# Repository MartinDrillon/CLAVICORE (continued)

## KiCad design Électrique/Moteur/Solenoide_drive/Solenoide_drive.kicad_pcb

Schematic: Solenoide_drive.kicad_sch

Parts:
C1, C4, C5, C9: 22uF; C_1206_3216Metric; Mouser Part Number 187-CL31A226KAHNNNE
C2, C3, C8, C10, C14, C15, C16, C17, C18, C19, C20, C21, C22, C23, C24, C25, C26, C29, C33, C35, C37, C39, C42, C45, C46, C48, C50, C51, C54, C56, C58, C60, C62, C63, C66, C68, C70, C73, C74, C75, C78, C82, C83, C84, C85, C86, C87, C88, C89, C98, C99, C104: 0.1uF; C_0402_1005Metric; Mouser Part Number 603-CC603KRX7R9BB104
C6: 75pF; C_0603_1608Metric; Manufacturer_Part_Number CC0402JRNPO9BN750
C7, C30, C36, C43, C47, C55, C59, C67, C71, C90, C91, C92, C93, C100: 10uF; C_1206_3216Metric; Mouser Part Number 187-CL31A106KBHNNNE
C11, C12, C13, C27: 4.7uF; C_0603_1608Metric
C28, C31, C34, C40, C41, C52, C53, C64, C65, C79, C80, C81: 22nF; C_0603_1608Metric
C32, C38, C44, C49, C57, C61, C69, C72, C94, C95, C96, C97, C101, C102: C680; CAP-SMD_BD12.5-L13.0-W13.0-LS14.4-FD; JLCPCB Part C90272
C76, C77: 15pF; C_0603_1608Metric; Mouser Part Number 187-CL10C150JB8NNNC
C103: EEE-FK1H100P; EEE1AA101SP; Mouser Part Number 667-EEE-FK1H100P
D1: SMCJ26CAHE3_A/H; DIOM7959X262N; Mouser Part Number 576-SMCJ28A
D2: SS14; D_SMA
F1: 0458010.DR; FUSC3216X158N; Mouser Part Number 576-0458010.DR
FB1: BLM18PG121SN1D; BLM18SP221SN1B; Mouser Part Number 81-BLM18PG121SN1D
IC1: SC1510_13_-A4; QFN40P1000X1000X90-81N-D; Manufacturer_Part_Number SC2212
IC2: TPS54302DDCR; SOT95P280X110-6N; Mouser Part Number 595-TPS54302DDCR
IC3: TLV1117-33IDCY; SOT230P700X180-4N; Mouser Part Number 595-TLV1117-33IDCY
IC4, IC5, IC6, IC7, IC8, IC9, IC10, IC11, IC13, IC14, IC15, IC16: DRV8874PWPR; SOP65P640X120-17N; Mouser Part Number 595-DRV8874PWPR
IC12: TCAN332DR; SOIC127P600X175-8N; Mouser Part Number 595-TCAN332DR
IC17: 74HC4067PW,118; SOP65P640X110-24N; Mouser Part Number 771-74HC4067PW-T
J1, J2, J3, J4, J5, J6, J7, J8, J12, J13, J14, J15: Conn_01x02_Pin; B2BXHAMLFSN; Mouser Part Number 306-B2B-XH-AMLFSNP
J9, J10, J17: Conn_01x02_Pin; SHDRRA2W50P0X200_1X2_600X770X525P; Mouser Part Number 306-B2B-XH-AMLFSNP
J11: 1729128; Mouser Part Number 651-1729128
J16: B4B-XH-A_LF__SN_; B4BXHALFSN; Mouser Part Number 306-B4BXHALFSN
L1: 10uH; SRP6060FA4R7M; Mouser Part Number 652-SRP6060FA-100M
L2: AOTA-B201610S3R3-101-T; AOTAB201610S3R3101T; Mouser Part Number 815-AB201610S3R3101T
R1: 510k; R_0603_1608Metric
R2, R4: 100k; R_0603_1608Metric; Mouser Part Number 303-0603WAF1003T5E
R3: 13K; R_0603_1608Metric
R5: 49.9; R_0603_1608Metric
R6: R33; R_0603_1608Metric
R7, R9, R11, R12, R15, R16, R19, R20, R25, R27, R29, R31, R34, R36: 10k; R_0603_1608Metric
R8, R10, R13, R14, R17, R18, R21, R22, R26, R28, R30, R32: 2,4k; R_0603_1608Metric; JLCPCB 0603WAF2401T5E
R23, R33, R35: R1K; R_0603_1608Metric
R24: R120; R_0603_1608Metric; not fitted
S1, S2: TS-1088-AR02016; TS1088AR02016; Manufacturer_Part_Number TS-1088-AR02016
TP1, TP2, TP3, TP7: TestPoint; TestPoint_Pad_D1.0mm_Silkless
TP4, TP5, TP6: TestPoint; TestPoint_Pad_D4.0mm_Silkless
Y1: ABM8-272-T3; ABM8272T3; Mouser Part Number 815-ABM8-272-T3

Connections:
3.3VIN: C1.1, C8.1, C12.1, C14.1, C15.1, C16.1, C17.1, C18.1, C19.1, C22.1, C23.1, C24.1, C25.1, C26.1, C37.1, C45.1, C48.1, C56.1, C60.1, C68.1, C73.1, C78.1, C98.1, D2.2 (A), IC1.5 (IOVDD_1), IC1.15 (IOVDD_2), IC1.24 (IOVDD_3), IC1.29 (IOVDD_4), IC1.41 (IOVDD_5), IC1.50 (IOVDD_6), IC1.59 (ADC_AVDD), IC1.60 (IOVDD_7), IC1.64 (VREG_VIN), IC1.68 (USB_OTP_VDD), IC1.69 (QSPI_IOVDD), IC1.76 (IOVDD_8), IC3.2 (OUTPUT_2), IC3.4 (OUTPUT), IC4.5 (VREF), IC5.5 (VREF), IC6.5 (VREF), IC7.5 (VREF), IC8.5 (VREF), IC9.5 (VREF), IC10.5 (VREF), IC11.5 (VREF), IC12.3 (VCC), IC13.5 (VREF), IC14.5 (VREF), IC15.5 (VREF), IC16.5 (VREF), IC17.24 (VCC), J16.2, R6.1, R7.2, R9.2, R11.2, R12.2, R15.2, R16.2, R19.2, R20.2, R25.2, R27.2, R29.2, R31.2, R34.2, R36.2, TP2.1 (1_1)
5VIN: C4.1, C5.1, C9.1, C10.1, D2.1 (K), IC3.3 (INPUT), J17.1, L1.2, R5.1, TP1.1 (1_1)
24VIN: C29.1, C30.1, C32.1, C33.2, C35.1, C36.1, C38.1, C39.2, C42.1, C43.1, C44.1, C46.1, C47.1, C49.1, C50.2, C51.2, C54.1, C55.1, C57.1, C58.1, C59.1, C61.1, C62.2, C63.2, C66.1, C67.1, C69.1, C70.1, C71.1, C72.1, C74.2, C75.2, C82.1, C83.1, C84.2, C85.2, C86.1, C87.1, C88.2, C89.2, C90.1, C91.1, C92.1, C93.1, C94.1, C95.1, C96.1, C97.1, C100.1, C101.1, C102.1, D1.1 (K), F1.1, FB1.1, IC4.11 (VM), IC5.11 (VM), IC6.11 (VM), IC7.11 (VM), IC8.11 (VM), IC9.11 (VM), IC10.11 (VM), IC11.11 (VM), IC13.11 (VM), IC14.11 (VM), IC15.11 (VM), IC16.11 (VM)
+1V1: C11.1, C20.1, C21.1, C27.1, IC1.10 (DVDD_1), IC1.32 (DVDD_2), IC1.51 (DVDD_3), IC1.65 (VREG_FB), L2.1, TP3.1 (1_1)
/ADC0: IC4.6 (IPROPI), IC17.22 (Y9), R8.1
/ADC1: IC6.6 (IPROPI), IC17.21 (Y10), R13.1
/ADC2: IC8.6 (IPROPI), IC17.20 (Y11), R17.1
/ADC3: IC10.6 (IPROPI), IC17.19 (Y12), R21.1
/ADC4: IC5.6 (IPROPI), IC17.18 (Y13), R10.1
/ADC5: IC7.6 (IPROPI), IC17.17 (Y14), R14.1
/ADC6: IC9.6 (IPROPI), IC17.8 (Y1), R18.1
/ADC7: IC11.6 (IPROPI), IC17.7 (Y2), R22.1
/ADC8: IC13.6 (IPROPI), IC17.4 (Y5), R26.1
/ADC9: IC14.6 (IPROPI), IC17.6 (Y3), R28.1
/ADC10: IC15.6 (IPROPI), IC17.5 (Y4), R30.1
/ADC11: IC16.6 (IPROPI), IC17.3 (Y6), R32.1
/Bouton test: C104.1, IC1.43 (GPIO34), R36.1, S2.1 (COM)
/FAULT0: IC1.48 (GPIO39), IC4.4 (NFAULT), R7.1
/FAULT1: IC1.46 (GPIO37), IC6.4 (NFAULT), R11.1
/FAULT2: IC1.1 (GPIO4), IC8.4 (NFAULT), R15.1
/FAULT3: IC1.80 (GPIO3), IC10.4 (NFAULT), R19.1
/FAULT4: IC1.11 (GPIO12), IC5.4 (NFAULT), R9.1
/FAULT5: IC1.8 (GPIO10), IC7.4 (NFAULT), R12.1
/FAULT6: IC1.17 (GPIO17), IC9.4 (NFAULT), R16.1
/FAULT7: IC1.16 (GPIO16), IC11.4 (NFAULT), R20.1
/FAULT8: IC1.26 (GPIO25), IC13.4 (NFAULT), R25.1
/FAULT9: IC1.22 (GPIO22), IC14.4 (NFAULT), R27.1
/FAULT10: IC1.39 (GPIO31), IC15.4 (NFAULT), R29.1
/FAULT11: IC1.36 (GPIO28), IC16.4 (NFAULT), R31.1
/FREQ OSC: IC1.52 (GPIO41_ADC1), TP7.1 (1_1)
/GND_TSP: IC2.1 (GND), R3.2
/MUX OUT: IC1.56 (GPIO45_ADC5), IC17.1 (Z)
/MUX_EN: IC1.53 (GPIO42_ADC2), IC17.15 (~E)
/PWM0: IC1.44 (GPIO35), IC4.1 (EN/IN1)
/PWM1: IC1.78 (GPIO1), IC6.1 (EN/IN1)
/PWM2: IC1.2 (GPIO5), IC8.1 (EN/IN1)
/PWM3: IC1.4 (GPIO7), IC10.1 (EN/IN1)
/PWM4: IC1.9 (GPIO11), IC5.1 (EN/IN1)
/PWM5: IC1.13 (GPIO14), IC7.1 (EN/IN1)
/PWM6: IC1.20 (GPIO20), IC9.1 (EN/IN1)
/PWM7: IC1.18 (GPIO18), IC11.1 (EN/IN1)
/PWM8: IC1.27 (GPIO26), IC13.1 (EN/IN1)
/PWM9: IC1.23 (GPIO23), IC14.1 (EN/IN1)
/PWM10: IC1.40 (GPIO32), IC15.1 (EN/IN1)
/PWM11: IC1.37 (GPIO29), IC16.1 (EN/IN1)
/RUN: C99.1, IC1.35 (RUN), R34.1, S1.1 (COM)
/RXD: IC1.57 (GPIO46_ADC6), IC12.4 (RXD)
/S0: IC1.55 (GPIO44_ADC4), IC17.10 (S0)
/S1: IC1.54 (GPIO43_ADC3), IC17.11 (S1)
/S2: IC1.47 (GPIO38), IC17.14 (S2)
/S3: IC1.45 (GPIO36), IC17.13 (S3)
/SDCLK: IC1.33 (SWCLK), J16.3
/SENS0: IC1.77 (GPIO0), IC4.2 (PH/IN2)
/SENS1: IC1.79 (GPIO2), IC6.2 (PH/IN2)
/SENS2: IC1.3 (GPIO6), IC8.2 (PH/IN2)
/SENS3: IC1.6 (GPIO8), IC10.2 (PH/IN2)
/SENS4: IC1.12 (GPIO13), IC5.2 (PH/IN2)
/SENS5: IC1.7 (GPIO9), IC7.2 (PH/IN2)
/SENS6: IC1.21 (GPIO21), IC9.2 (PH/IN2)
/SENS7: IC1.19 (GPIO19), IC11.2 (PH/IN2)
/SENS8: IC1.28 (GPIO27), IC13.2 (PH/IN2)
/SENS9: IC1.25 (GPIO24), IC14.2 (PH/IN2)
/SENS10: IC1.42 (GPIO33), IC15.2 (PH/IN2)
/SENS11: IC1.38 (GPIO30), IC16.2 (PH/IN2)
/SWDIO: IC1.34 (SWDIO), J16.4
/TXD: IC1.58 (GPIO47_ADC7), IC12.1 (TXD)
/VREG AVDD: C13.1, IC1.61 (VREG_AVDD), R6.2
/VREG LX: IC1.63 (VREG_LX), L2.2
/XIN: C76.1, IC1.30 (XIN), Y1.1 (CRYSTAL_1)
/XOUT: IC1.31 (XOUT), R23.1
/nSLEEP: IC1.14 (GPIO15), IC4.3 (NSLEEP), IC5.3 (NSLEEP), IC6.3 (NSLEEP), IC7.3 (NSLEEP), IC8.3 (NSLEEP), IC9.3 (NSLEEP), IC10.3 (NSLEEP), IC11.3 (NSLEEP), IC13.3 (NSLEEP), IC14.3 (NSLEEP), IC15.3 (NSLEEP), IC16.3 (NSLEEP)
CAN+: IC12.7 (CANH), J9.2, J10.1, R24.1
CAN-: IC12.6 (CANL), J9.1, J10.2, R24.2
GND: C1.2, C2.2, C4.2, C5.2, C7.2, C8.2, C9.2, C10.2, C11.2, C12.2, C13.2, C14.2, C15.2, C16.2, C17.2, C18.2, C19.2, C20.2, C21.2, C22.2, C23.2, C24.2, C25.2, C26.2, C27.2, C30.2, C32.2, C33.1, C36.2, C37.2, C38.2, C39.1, C43.2, C44.2, C45.2, C47.2, C48.2, C49.2, C50.1, C51.1, C55.2, C56.2, C57.2, C59.2, C60.2, C61.2, C62.1, C63.1, C67.2, C68.2, C69.2, C71.2, C72.2, C73.2, C74.1, C75.1, C76.2, C77.2, C78.2, C84.1, C85.1, C88.1, C89.1, C90.2, C91.2, C92.2, C93.2, C94.2, C95.2, C96.2, C97.2, C98.2, C99.2, C100.2, C101.2, C102.2, C103.2 (-), C104.2, D1.2 (A), IC1.62 (VREG_PGND), IC1.81 (GND), IC3.1 (ADJ/GND), IC4.7 (IMODE), IC4.9 (PGND), IC4.15 (GND), IC4.16 (PMODE), IC4.17 (EP), IC5.7 (IMODE), IC5.9 (PGND), IC5.15 (GND), IC5.16 (PMODE), IC5.17 (EP), IC6.7 (IMODE), IC6.9 (PGND), IC6.15 (GND), IC6.16 (PMODE), IC6.17 (EP), IC7.7 (IMODE), IC7.9 (PGND), IC7.15 (GND), IC7.16 (PMODE), IC7.17 (EP), IC8.7 (IMODE), IC8.9 (PGND), IC8.15 (GND), IC8.16 (PMODE), IC8.17 (EP), IC9.7 (IMODE), IC9.9 (PGND), IC9.15 (GND), IC9.16 (PMODE), IC9.17 (EP), IC10.7 (IMODE), IC10.9 (PGND), IC10.15 (GND), IC10.16 (PMODE), IC10.17 (EP), IC11.7 (IMODE), IC11.9 (PGND), IC11.15 (GND), IC11.16 (PMODE), IC11.17 (EP), IC12.2 (GND), IC13.7 (IMODE), IC13.9 (PGND), IC13.15 (GND), IC13.16 (PMODE), IC13.17 (EP), IC14.7 (IMODE), IC14.9 (PGND), IC14.15 (GND), IC14.16 (PMODE), IC14.17 (EP), IC15.7 (IMODE), IC15.9 (PGND), IC15.15 (GND), IC15.16 (PMODE), IC15.17 (EP), IC16.7 (IMODE), IC16.9 (PGND), IC16.15 (GND), IC16.16 (PMODE), IC16.17 (EP), IC17.12 (GND), J11.2, J16.1, J17.2, R2.1, R8.2, R10.2, R13.2, R14.2, R17.2, R18.2, R21.2, R22.2, R26.2, R28.2, R30.2, R32.2, R33.1, R35.1, TP4.1 (1_1), TP5.1 (1_1), TP6.1 (1_1), Y1.2 (GND_1), Y1.4 (GND_2)
unnamed: C6.2, R4.2, R5.2
unnamed: C2.1, C7.1, C103.1 (+), FB1.2, IC2.3 (VIN), R1.1
unnamed: F1.2, J11.1
unnamed: C3.2, IC2.6 (BOOT)
unnamed: IC2.5 (EN), R1.2, R2.2
unnamed: C6.1, IC2.4 (FB), R3.1, R4.1
unnamed: C3.1, IC2.2 (SW), L1.1
unnamed: C28.2, IC4.13 (CPH)
unnamed: C28.1, IC4.14 (CPL)
unnamed: IC4.8 (OUT1), J1.1
unnamed: IC4.10 (OUT2), J1.2
unnamed: C29.2, IC4.12 (VCP)
unnamed: C34.2, IC5.13 (CPH)
unnamed: C34.1, IC5.14 (CPL)
unnamed: IC5.8 (OUT1), J2.1
unnamed: IC5.10 (OUT2), J2.2
unnamed: C35.2, IC5.12 (VCP)
unnamed: C40.2, IC6.13 (CPH)
unnamed: C40.1, IC6.14 (CPL)
unnamed: IC6.8 (OUT1), J3.1
unnamed: IC6.10 (OUT2), J3.2
unnamed: C42.2, IC6.12 (VCP)
unnamed: C41.2, IC7.13 (CPH)
unnamed: C41.1, IC7.14 (CPL)
unnamed: IC7.8 (OUT1), J4.1
unnamed: IC7.10 (OUT2), J4.2
unnamed: C46.2, IC7.12 (VCP)
unnamed: C52.2, IC8.13 (CPH)
unnamed: C52.1, IC8.14 (CPL)
unnamed: IC8.8 (OUT1), J5.1
unnamed: IC8.10 (OUT2), J5.2
unnamed: C54.2, IC8.12 (VCP)
unnamed: C53.2, IC9.13 (CPH)
unnamed: C53.1, IC9.14 (CPL)
unnamed: IC9.8 (OUT1), J6.1
unnamed: IC9.10 (OUT2), J6.2
unnamed: C58.2, IC9.12 (VCP)
unnamed: C64.2, IC10.13 (CPH)
unnamed: C64.1, IC10.14 (CPL)
unnamed: IC10.8 (OUT1), J7.1
unnamed: IC10.10 (OUT2), J7.2
unnamed: C66.2, IC10.12 (VCP)
unnamed: C65.2, IC11.13 (CPH)
unnamed: C65.1, IC11.14 (CPL)
unnamed: IC11.8 (OUT1), J8.1
unnamed: IC11.10 (OUT2), J8.2
unnamed: C70.2, IC11.12 (VCP)
unnamed: C31.2, IC13.13 (CPH)
unnamed: C31.1, IC13.14 (CPL)
unnamed: IC13.8 (OUT1), J12.1
unnamed: IC13.10 (OUT2), J12.2
unnamed: C82.2, IC13.12 (VCP)
unnamed: C79.2, IC14.13 (CPH)
unnamed: C79.1, IC14.14 (CPL)
unnamed: IC14.8 (OUT1), J13.1
unnamed: IC14.10 (OUT2), J13.2
unnamed: C83.2, IC14.12 (VCP)
unnamed: C80.2, IC15.13 (CPH)
unnamed: C80.1, IC15.14 (CPL)
unnamed: IC15.8 (OUT1), J14.1
unnamed: IC15.10 (OUT2), J14.2
unnamed: C86.2, IC15.12 (VCP)
unnamed: C81.2, IC16.13 (CPH)
unnamed: C81.1, IC16.14 (CPL)
unnamed: IC16.8 (OUT1), J15.1
unnamed: IC16.10 (OUT2), J15.2
unnamed: C87.2, IC16.12 (VCP)
unnamed: R33.2, S1.2 (NO)
unnamed: R35.2, S2.2 (NO)
unnamed: C77.1, R23.2, Y1.3 (CRYSTAL_2)

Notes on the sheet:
FLASH
LDO
Crystal 12Mhz
CAN
13k au lieu de 13.3 pour utiliser une référence basic > 5,18V en sortie
MUX
Buck
Alim + protection + bulk
RP2548B
DRIVER
Tests points
Sortie alim pour la carte clavier

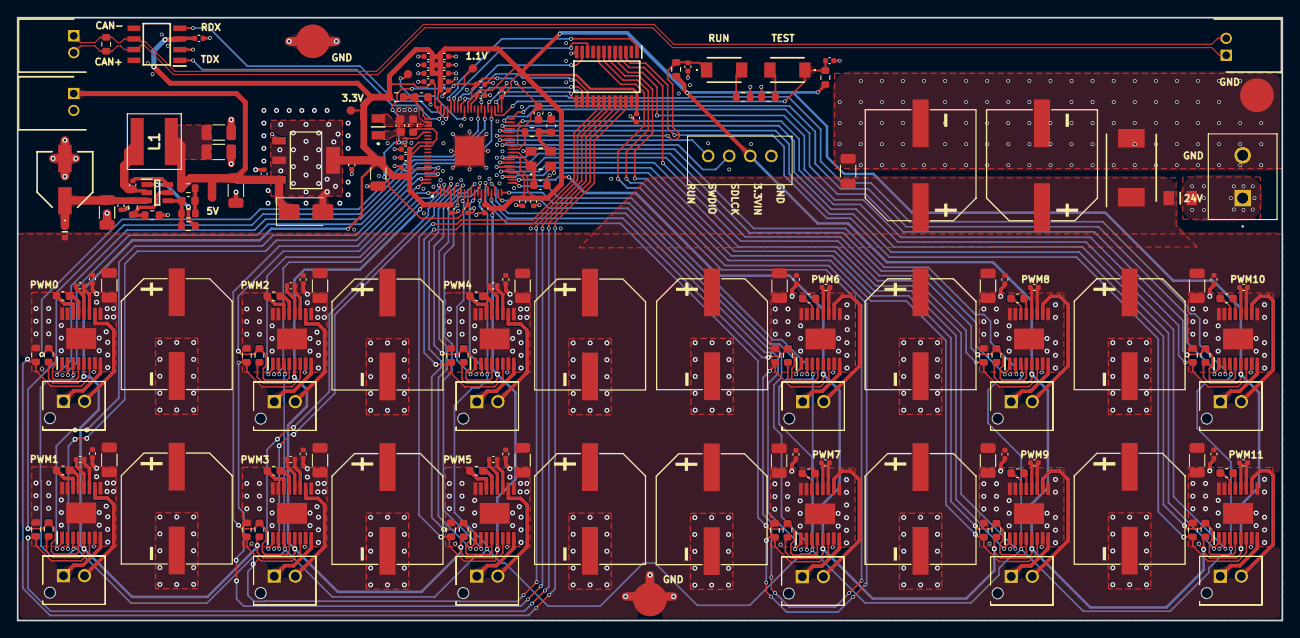
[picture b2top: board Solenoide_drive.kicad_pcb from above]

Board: 4 copper layers, 150.0 x 71.5 mm, 190 parts (0 on the bottom side), 144 nets.
